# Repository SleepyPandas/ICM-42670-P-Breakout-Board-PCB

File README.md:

<h1 align="center">ICM-42670-P Motion Sensor Breakout Board</h1>

<p align="center">
  <strong>A compact, breadboard-friendly breakout for the TDK InvenSense ICM-42670-P 6-axis IMU</strong><br/>
  Designed in KiCad 10.0 · Rev v1.4 · By ME! SleepyPandas / Anthony 
  <br>
  <br>
  
</p>

<p align="center">

</p>

---

## Revision notes for v1.3 , v1.4 
Has to do with component selection for DFM and Cleaning up Traces (no Major Functional Changes) 

## Revision Notes (v1.2)

- Primary project update is now the **0603 parts variant** (easier hand assembly than 0402 passives)
- Passive footprints moved to **0603** across the v1.2 schematic/PCB
- Dedicated v1.2 manufacturing outputs are included in `0603 Parts/production/` (BOM, positions, designators, IPC netlist)
- Project/schematic revision fields updated to **v1.2** in the 0603 KiCad project

---

## Board Gallery

<table>
  <tr>
    <td align="center" width="70%"><strong>3D Render</strong></td>
    <td align="center" width="30%"><strong>PCB Layout</strong></td>
  </tr>
  <tr>
    <td valign="middle"></td>
    <td valign="middle"></td>

  </tr>
  <tr>
    <td align="center" colspan="2"><strong>Schematic</strong></td>
  </tr>
  <tr>
    <td colspan="2"></td>
  </tr>

  <tr>
    <td align="center" colspan="2"><strong>Prototyping</strong></td>
  </tr>

  <tr>
    <td colspan="2"></td>
  </tr>
</table>

---

## Features

| Feature | Detail |
|:---|:---|
| **IMU** | ICM-42670-P, 6-axis (3-axis accel + 3-axis gyro), LGA-14 package |
| **Power** | On-board **MCP1700x** LDO regulator (SOT-23), accepts up to 6V input |
| **Interfaces** | I²C / I3C / SPI, directly broken out to 0.1″ header pins with on-board I²C pull-ups |
| **Signals** | VCC · GND · CS · INT2 · SCL · SDA · SDO · INT1 · FSYNC |
| **Assembly** | v1.2 updates passives to **0603** package sizing |
| **Indicator** | Power LED with 120Ω current-limiting resistor |
| **Form Factor** | Breadboard-friendly with standard 2.54mm pitch headers |

---

## ICM-42670-P Pinout (Official TDK Signal Descriptions)

| Pin | Name | Description |
|:---:|:---|:---|
| 1 | **AP_SDO / AP_AD0** | SPI serial data output (4-wire); I2C slave address LSB |
| 2 | **RESV** | No connect, or connect to GND / VDDIO |
| 3 | **RESV** | No connect, or connect to GND / VDDIO |
| 4 | **INT1 / INT** | Interrupt 1 (push-pull or open drain); all interrupts can map here |
| 5 | **VDDIO** | IO power supply voltage |
| 6 | **GND** | Power supply ground |
| 7 | **FSYNC** | Frame sync input; connect to GND if unused |
| 8 | **VDD** | Power supply voltage |
| 9 | **INT2** | Interrupt 2 (push-pull or open drain) |
| 10 | **RESV** | No connect, or connect to GND / VDDIO |
| 11 | **RESV** | No connect, or connect to GND / VDDIO |
| 12 | **AP_CS** | SPI chip select; connect to VDDIO if using I2C |
| 13 | **AP_SCL / AP_SCLK** | I2C serial clock / SPI serial clock |
| 14 | **AP_SDA / AP_SDIO / AP_SDI** | I2C serial data; SPI data I/O (3-wire) or SPI data input (4-wire) |

---

## Circuit Design Highlights

### Power Regulation
- **MCP1700x** LDO provides a clean regulated rail from a wide input range
- **3.3V rail target** using MCP1700x-330xxTT is maintained at the board's expected low load current
- **2.2µF** input & output capacitors (C4, C5) for LDO stability, Microchip's datasheet recommends >= to 1µF but for simplicity we use the same 2.2µF used in other parts of the circuit. 
- Power LED (D1) with **120Ω** series resistor for visual power indication

### Assembly/Footprint Update (v1.2)

- Passives are standardized to **0603** packages in the v1.2 project for easier hand soldering
- Sensor and regulator footprints remain compact: **LGA-14** (U1) and **SOT-23** (U3)

### Decoupling Strategy

- **C1 (0.1µF)**, High-frequency bypass on VDD, placed closest to IC power pin high-frequency filtering
- **C2 (2.2µF)**, Bulk decoupling on VDD for low-frequency noise filtering
- **C3 (10nF)**, VDDIO Noise Reduction / decoupling from SDA SCL

> [!NOTE] 
> **Layout note:** Decoupling caps are placed as close to the ICM-42670-P power pins as physically possible to minimize parasitic loop inductance (i.e where the trace is the limiting factor for power not the capacitor) Leading to unexpected behavior for sensitive IMUs.

### Interface Configuration
- **SDA -> 10kΩ pull-up to 3V3_Clean** for I²C/I3C bus idle-high behavior
- **SCL -> 10kΩ pull-up to 3V3_Clean** for I²C/I3C clock line idle-high behavior
- **CS -> 10kΩ pull-up to VDDIO**, boots into I²C/I3C mode by default
- **FSYNC -> 10kΩ pull-down to GND**, disables frame sync when not driven
- **SDO/AD0 -> direct breakout (no fixed pull resistor)** for maximum SPI flexibility

> [!NOTE] 
> **Note:** The I²C pull-ups are on SDA/SCL only; this keeps I²C and I3C ready out-of-the-box while avoiding direct loading on SPI MISO paths.

---

## Bill of Materials

| Ref | Value | Specification | Package / FootPrint | Description | Qty |
|:---:|:---:|:---:|:---:|:---|:---:|
| U1 | ICM-42670-P | - | LGA-14 (2.5x3mm) | 6-axis IMU (accel + gyro) | 1 |
| U3 | MCP1700x-330xxTT | 250mA LDO, SOT-23 | SOT-23 | Regulated 3.3V supply rail | 1 |
| C1 | 100nF | X7R, ±10%, 16V | 0603 | VDD high-freq bypass | 1 |
| C2, C4, C5 | 2.2µF | X7R, ±10%, 16V | 0603 | VDD bulk / LDO I/O caps | 3 |
| C3 | 10nF | X7R, ±10%, 50V | 0603 | VDDIO bypass | 1 |
| R1, R2, R4, R5 | 10kΩ | ±1%, 50V | 0603 | CS pull-up / FSYNC pull-down / SDA & SCL pull-ups | 4 |
| R3 | 120Ω | ±1%, 50V | 0603 | LED current limiter | 1 |
| D1 | LED | - | 0603 | Power indicator | 1 |
| J2 | N/A | - | 2.54mm header | 9-pin breakout connector | 1 |

---

## Design Decisions

---

**1. On-Board I2C Pull-ups Added (R4, R5)**

I2C pull-ups are required because I2C uses open-drain signaling and the bus needs passive pull-up resistors to reach logic HIGH. In this revision, dedicated **10kΩ pull-ups were added on SDA and SCL** so the board is immediately usable in I2C and I3C-style wiring. This keeps the breakout more plug-and-play while still preserving speed-focused SPI behavior, since the pull-ups are only on SDA/SCL and not on the SPI data output path.

---

**2. LDO (Low-Dropout Regulator) vs. No Regulator**

The ICM-42670-P officially supports 1.71–3.6V DC directly, so a regulator is not strictly required. But I included an MCP1700x LDO and selected a **3.3V output variant (MCP1700x-330xxTT)** for two reasons:

1. Most common dev boards (ESP32, Arduino, STM32) operate from 5V USB power rails. The [MCP1700 accepts 2.3-6.0V](https://ww1.microchip.com/downloads/en/DeviceDoc/MCP1700-Data-Sheet-20001826F.pdf) input and provides a clean regulated rail, making this breakout plug-and-play with virtually any platform.
2. The ICM-42670-P contains sensitive MEMS structures (accelerometer and gyroscope masses). The LDO provides a low-noise regulated rail, reducing supply-noise-induced measurement error. With expected draw of roughly **0.65mA (IMU) + ~3mA (power LED) ≈ 3.65mA total**, the 3.3V LDO is operating at a very light load and still provides a approximately 3.3V output with a 3.3V input however will not provide the noise reduction benefits at that voltage only 5V.

---

**3. SDO/AD0 Configuration for Speed Flexibility**

In this revision, **SDO/AD0 is left without a fixed pull resistor** so the line can be defined by the host design. For I2C/I3C use, address selection can still be handled externally as needed.

In SPI mode, SDO becomes the MISO line. Avoiding a permanent pull resistor helps preserve edge rate and signal integrity at higher SPI clock speeds.

---

**4. Capacitor Placement and Choice**

Capacitors C1 (100nF) and C2 (2.2µF) are placed as close as physically possible to the ICM-42670-P VDD pin to minimize trace inductance in the power delivery loop. C3 (10nF) decouples VDDIO. Together they filter both high-frequency noise and lower-frequency supply droop, keeping the power rails clean for the MEMS core.

---

**5. Chip Select (CS) Pull-Up**

CS is pulled HIGH via a 10kΩ resistor to VDDIO by default. This ensures the ICM-42670-P boots into I2C/I3C mode rather than entering an undefined mode at startup. Users wishing to use SPI simply drive CS LOW from the microcontroller; the pull-up is weak enough to be overridden during normal SPI operation.

---

## Repository Structure

```
ICM-42670-P Breakout Board
├──  Draw.kicad_wks                            # Custom KiCad worksheet
├──  PersonalNotes.md                          # Project notes
├──  Models Photos PDFS/                       # Renders, schematics exports, documentation
├──  production/                               # Top-level fabrication outputs
│   ├── bom.csv
│   ├── designators.csv
│   ├── netlist.ipc
│   ├── positions.csv
│   └── backups/
├──  Schematic PCB Design/                     # Active v1.2 (0603) design files
│   ├── ICM-42670-P Breakout Board 0603.kicad_sch
│   ├── ICM-42670-P Breakout Board 0603.kicad_pcb
│   ├── ICM-42670-P Breakout Board 0603.kicad_pro
│   ├── ICM-42670-P Breakout Board 0603.csv
│   ├── production/                            # v1.2 fabrication outputs
│   │   ├── bom.csv
│   │   ├── designators.csv
│   │   ├── netlist.ipc
│   │   ├── positions.csv
│   │   └── backups/
│   └── ICM-42670-P Breakout Board 0603-backups/
├──  V1 Old 0402 Design/                       # Legacy 0402 design archive
│   ├── ICM-42670-P Breakout Board.kicad_sch
│   ├── ICM-42670-P Breakout Board.kicad_pcb
│   ├── ICM-42670-P Breakout Board.kicad_pro
│   └── PCB PANEL Production/                  # Panelized legacy production design
├──  ICM-42670-P Breakout Board-backups/
└──  README.md
```

---

## Tools Used

- **[KiCad 10.0](https://www.kicad.org/)**, Schematic & PCB layout
- **JLCPCB**, PCBA service
- **OSH Park**, PCB Fabrication (Really cheap 3$ for 3 Boards)
- Shoutout to Altium Designer... Costs an arm and a leg

## 

Designed by me! SleepyPandas

---

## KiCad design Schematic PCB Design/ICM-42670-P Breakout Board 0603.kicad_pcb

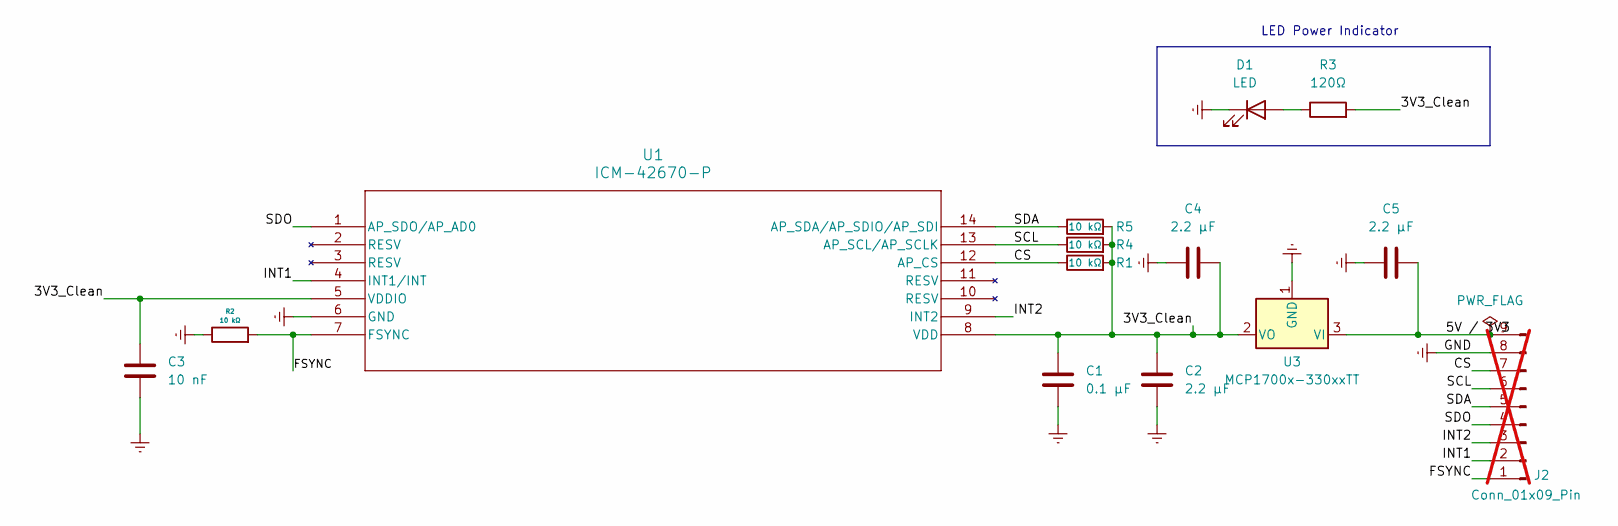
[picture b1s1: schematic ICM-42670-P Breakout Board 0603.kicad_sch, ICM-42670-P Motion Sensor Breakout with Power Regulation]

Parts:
C1: 0.1 µF; C_0603_1608Metric; JLCPCB Part # C1525
C2, C4, C5: 2.2 µF; C_0603_1608Metric; JLCPCB Part # C12530
C3: 10 nF; C_0603_1608Metric; JLCPCB Part # C15195
D1: LED; LED_0603_1608Metric; JLCPCB Part # C2290
J2: Conn_01x09_Pin; PinHeader_1x09_P2.54mm_Vertical; not fitted
R1, R2, R4, R5: 10 kΩ; R_0603_1608Metric; JLCPCB Part # C328298
R3: 120Ω; R_0603_1608Metric; JLCPCB Part # C352482
U1: ICM-42670-P; LGA14_2.5X3X0.76_IVS; JLCPCB Part # C3288646
U3: MCP1700x-330xxTT; SOT-23

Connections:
/3V3_Clean: C1.1, C2.1, C3.1, C4.2, R1.2, R3.2, R4.2, R5.2, U1.5 (VDDIO), U1.8 (VDD), U3.2 (VO)
/5V / 3V3: C5.2, J2.9, U3.3 (VI)
/CS: J2.7, R1.1, U1.12 (AP_CS)
/FSYNC: J2.1, R2.2, U1.7 (FSYNC)
/INT1: J2.2, U1.4 (INT1/INT)
/INT2: J2.3, U1.9 (INT2)
/SCL: J2.6, R4.1, U1.13 (AP_SCL/AP_SCLK)
/SDA: J2.5, R5.1, U1.14 (AP_SDA/AP_SDIO/AP_SDI)
/SDO: J2.4, U1.1 (AP_SDO/AP_AD0)
GND: C1.2, C2.2, C3.2, C4.1, C5.1, D1.1 (K), J2.8, R2.1, U1.6 (GND), U3.1 (GND)
unnamed: D1.2 (A), R3.1

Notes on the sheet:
LED Power Indicator

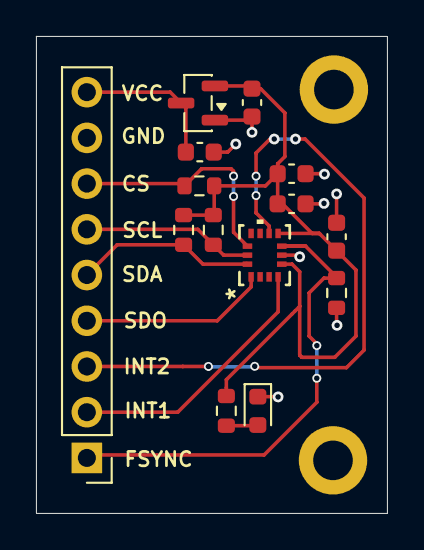
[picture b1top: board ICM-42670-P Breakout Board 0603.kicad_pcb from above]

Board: 2 copper layers, 19.5 x 26.5 mm, 14 parts (0 on the bottom side), 11 nets.

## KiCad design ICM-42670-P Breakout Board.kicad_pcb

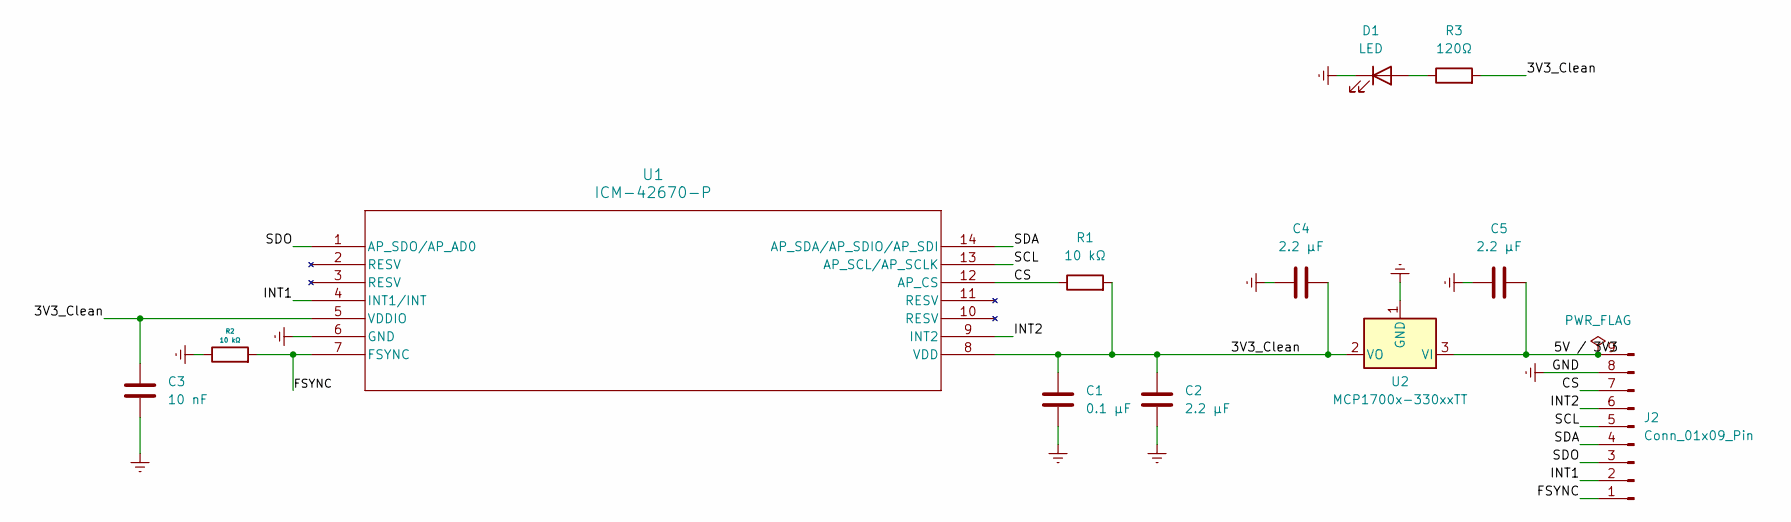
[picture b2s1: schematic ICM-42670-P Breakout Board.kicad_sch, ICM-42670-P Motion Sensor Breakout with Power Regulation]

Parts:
C1: 0.1 µF; C_0402_1005Metric; JLCPCB Part # C1525
C2, C4, C5: 2.2 µF; C_0402_1005Metric; JLCPCB Part # C12530
C3: 10 nF; C_0402_1005Metric; JLCPCB Part # C15195
D1: LED; LED_0603_1608Metric; JLCPCB Part # C2290
J2: Conn_01x09_Pin; PinHeader_1x09_P2.54mm_Vertical
R1, R2: 10 kΩ; R_0402_1005Metric; JLCPCB Part # C328298
R3: 120Ω; R_0402_1005Metric; JLCPCB Part # C352482
U1: ICM-42670-P; LGA14_2.5X3X0.76_IVS; JLCPCB Part # C3288646
U2: MCP1700x-330xxTT; SOT-23; JLCPCB Part # C39051

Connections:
/3V3_Clean: C1.1, C2.1, C3.1, C4.2, R1.2, R3.2, U1.5 (VDDIO), U1.8 (VDD), U2.2 (VO)
/5V / 3V3: C5.2, J2.9, U2.3 (VI)
/CS: J2.7, R1.1, U1.12 (AP_CS)
/FSYNC: J2.1, R2.2, U1.7 (FSYNC)
/INT1: J2.2, U1.4 (INT1/INT)
/INT2: J2.6, U1.9 (INT2)
/SCL: J2.5, U1.13 (AP_SCL/AP_SCLK)
/SDA: J2.4, U1.14 (AP_SDA/AP_SDIO/AP_SDI)
/SDO: J2.3, U1.1 (AP_SDO/AP_AD0)
GND: C1.2, C2.2, C3.2, C4.1, C5.1, D1.1 (K), J2.8, R2.1, U1.6 (GND), U2.1 (GND)
unnamed: D1.2 (A), R3.1

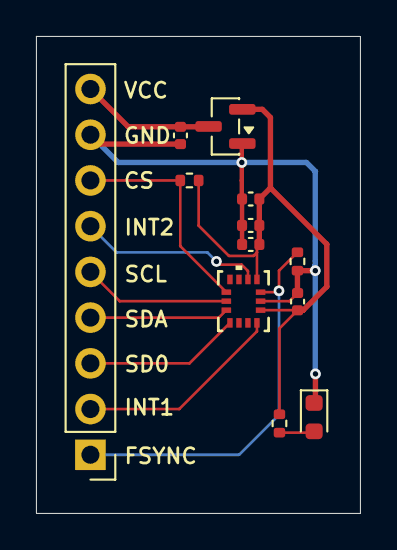
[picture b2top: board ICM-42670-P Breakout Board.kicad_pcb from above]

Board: 2 copper layers, 18.0 x 26.5 mm, 12 parts (0 on the bottom side), 11 nets.

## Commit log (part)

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2026-03-07 Initial Commit of ICM-42688-P with plans to modify to fit 42670-P
    Due to Supply Issues
2026-03-07 Swaped 42688 Sensor for 42670 added Conn_01x9
    Swaped 42688 Sensor for 42670 added Conn_01x9
    conn_01x9 Includes footprint
2026-03-07 Wired FSYNC with Pull down ground
    Wired FSYNC with Pull down ground
2026-03-07 Added Missing Footprints
2026-03-07 Changed Capacitor for Voltage Regulators to 2.2 microFarads for better part selection and reduce part complexity
2026-03-07 ADD drawing file
2026-03-07 Got rid of Resistor on SDO
    SDO resister can interfere with SPI and i3C comms, better to let MCU or user Control it
2026-03-07 Got rid of Pull down Resistor for INT2
2026-03-07 Traces Routed
2026-03-07 Added SilkScreen Text
2026-03-08 Add Indicator LED
2026-03-08 Update LED PART
2026-03-08 Wired LED
2026-03-08 Fix SilkScreen Errors
2026-03-08 Add JLCPCB Part#
2026-03-08 Generate Gerber Files For Production
2026-03-08 ICM-42670-P correction
2026-03-08 Add image to README for breakout board
    Added image to README for ICM-42670-P Breakout Board.
2026-03-08 Update image for ICM-42670-P Breakout Board
    Replaced old image with a new one for the ICM-42670-P Breakout Board.
2026-03-08 Add Paneled PCB version for PROD
2026-03-08 Changed BOM
    Bom Reflects General Parts now
2026-03-08 Adjusted schematic Page
    A
2026-03-08 Update image link for ICM-42670-P Breakout Board
2026-03-08 Add additional image to README
2026-03-08 Added Additional PCB, Schematic Photos and PDF pages
    moved Breakout Board Panel into seperate folder
2026-03-08 remove kicad-push
2026-03-08 Move Fab tools into Production Folder
2026-03-09 Revise README for ICM-42670-P Breakout Board
2026-03-09 Changed Paper Size
2026-03-09 Change 3D Render image in README.md
    Updated the image source for the 3D Render in the README.
2026-03-10 Added a Revision for V1.1 0603 from 0402
2026-03-11 Added 0603 form Factor Design
2026-03-11 Fix DRC errors
2026-03-11 DNP update on connector x9 pins
2026-03-11 add b.silkscreen text
2026-03-11 Gerber Files
2026-03-24 Added Orthogonal Dimensions
2026-03-26 Upgrade to KiCad 10.0
2026-03-26 Added 2 Pull Up Capacitors for I2C SDA SCL
2026-03-26 Updated PCB and Schematic to include Pull Ups for SCK SDA I2c
2026-03-26 Update README with new revision and images
    Updated revision number and replaced images for 3D render, PCB layout, and schematic.
2026-03-26 Added Descriptor for LED Power Indicator
2026-03-26 Clean up redundant Traces / tracks
2026-03-26 Added 1.2V versioning to PCB
2026-03-28 FIX: Adjusted Fsync Silkscreen to correct position
2026-03-28 Cleaned Up old V1 Design file structure
2026-03-28 Update Gitignore
2026-03-28 Add Load vs Dropout Voltage images to README
    Added images for Load vs Dropout Voltage graphs to README.
2026-03-28 Adjust image widths in README.md
    Updated image widths for better alignment in README.
2026-04-02 Swap CS and INT2 Pins
2026-04-02 Changed Pin outs
2026-04-03 Moved around Nets for better trace routing
2026-04-03 Rerouted Traces and Added Ground Plane
2026-04-03 Add Mounting holes M2
2026-04-03 Removed Old Version Files
2026-04-03 Bump V1.3
2026-04-03 Remove Old V1 0402 Designs
2026-04-03 Removed Via from 3V3 To reduce inductance
2026-04-03 Remove My name Put sleepypandas
2026-04-03 Subtract silk mask from Vias
2026-04-06 Changed Revision to 1.3V And Changed JLCPCB part numbers
2026-04-20 Add prototyping section to README
    Added prototyping section with an image in README.
2026-05-08 Update images in README for 3D Render and PCB Layout
2026-05-10 Update README with revision changes to v1.4
    Updated revision number and added notes for v1.3 and v1.4.
